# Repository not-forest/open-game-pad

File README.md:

# Open Game Pad

Low-cost, DIY game controller. This project enables anyone to build a custom game pad using affordable components and open hardware principles. The repository contains all necessary files, including PCB designs and firmware.

## Contents
- `pcb/`: PCB design files
- `src/`: Firmware source code
- `usbdrv/`: USB driver files
- `docs/`: Images

## Images

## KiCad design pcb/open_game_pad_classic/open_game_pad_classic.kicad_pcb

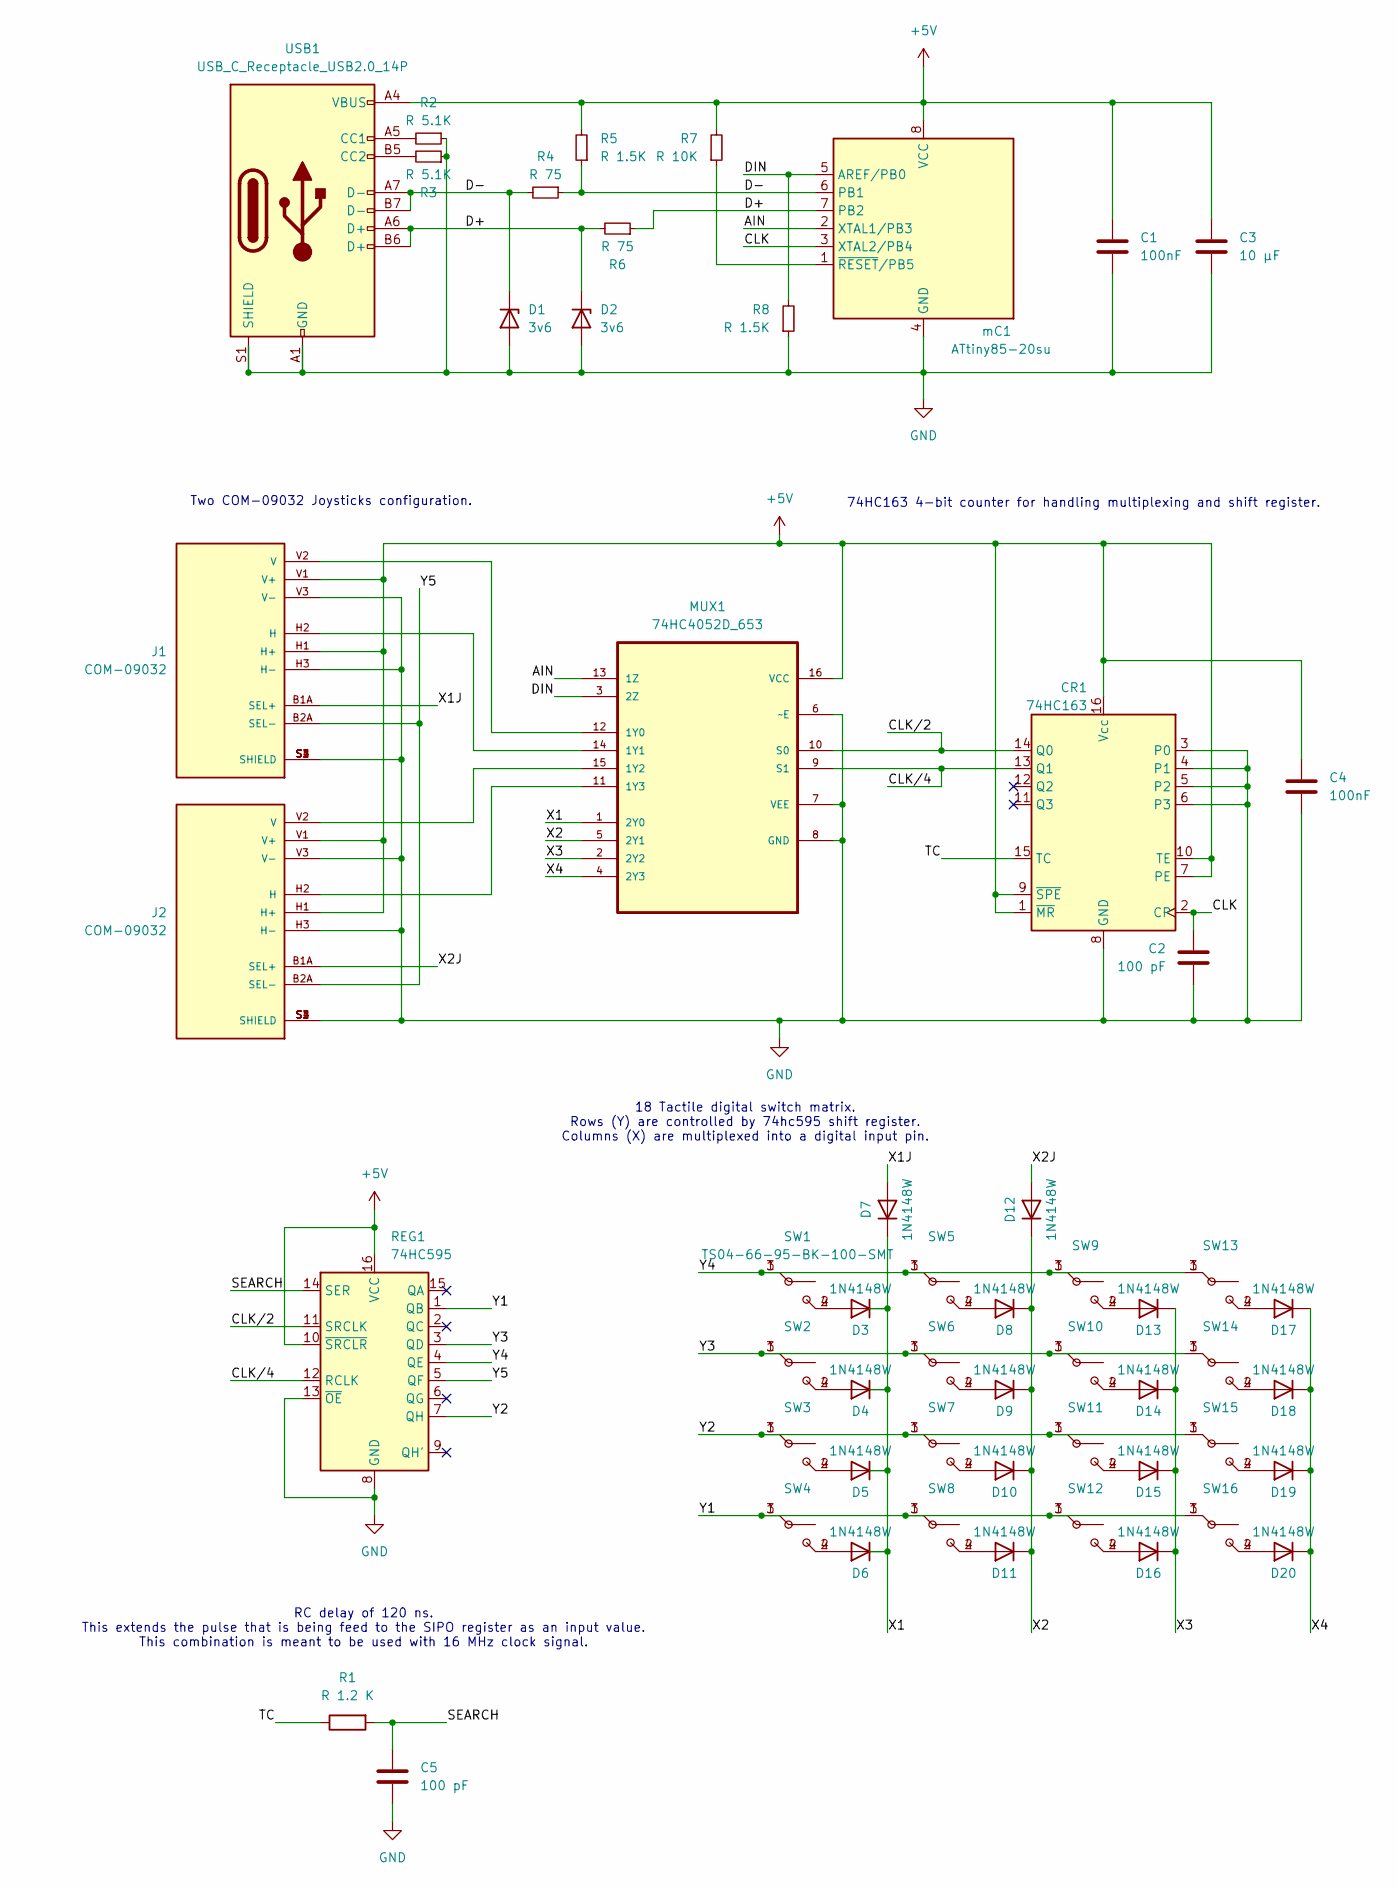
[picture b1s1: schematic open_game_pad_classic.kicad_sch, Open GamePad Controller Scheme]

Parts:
C1, C4: 100nF; C_0402_1005Metric
C2, C5: 100 pF; C_0402_1005Metric
C3: 10 µF; C_0402_1005Metric
CR1: 74HC163; SOIC127P600X175-16N
D1: 3v6; D_0201_0603Metric
D2: 3v6; D_0603_1608Metric
D3, D4, D5, D6, D7, D8, D9, D10, D11, D12, D13, D14, D15, D16, D17, D18, D19, D20: 1N4148W; D_SOD-123
J1, J2: COM-09032; XDCR_COM-09032; PARTREV N/A
MUX1: 74HC4052D_653; SOIC127P600X175-16N; MPN 74HC4052D,653
R1: R 1.2 K; R_0201_0603Metric
R2, R3: R 5.1K; R_0402_1005Metric
R4, R6: R 75; R_0201_0603Metric
R5: R 1.5K; R_0201_0603Metric
R7: R 10K; R_0402_1005Metric
R8: R 1.5K; R_0402_1005Metric
REG1: 74HC595; SOIC127P600X175-16N
SW1: TS04-66-95-BK-100-SMT; SW_TS04-66-95-BK-100-SMT
SW2, SW3, SW4, SW5, SW6, SW7, SW8, SW9, SW10, SW11, SW12, SW13, SW14, SW15, SW16: SW_TS04-66-95-BK-100-SMT
USB1: USB_C_Receptacle_USB2.0_14P; USB_C_Receptacle_HCTL_HC-TYPE-C-16P-01A
mC1: ATtiny85-20su; SOIC127P798X216-8N

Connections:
+5V: C1.1, C3.1, C4.1, CR1.1 (~MR), CR1.7 (PE), CR1.9 (~SPE), CR1.10 (TE), CR1.16 (Vcc), J1.H1 (H+), J1.V1 (V+), J2.H1 (H+), J2.V1 (V+), MUX1.16 (VCC), R5.2, R7.2, REG1.10 (~SRCLR), REG1.16 (VCC), USB1.A4 (VBUS), USB1.A9 (VBUS), USB1.B4 (VBUS), USB1.B9 (VBUS), mC1.8 (VCC)
/AIN: MUX1.13 (1Z), mC1.2 (XTAL1/PB3)
/CLK: C2.1, CR1.2 (CP), mC1.3 (XTAL2/PB4)
/CLK/2: CR1.14 (Q0), MUX1.10 (S0), REG1.11 (SRCLK)
/CLK/4: CR1.13 (Q1), MUX1.9 (S1), REG1.12 (RCLK)
/D+: D2.1 (K), R6.1, R6.2, USB1.A6 (D+), USB1.B6 (D+), mC1.7 (PB2)
/D-: D1.1 (K), R4.1, R4.2, R5.1, USB1.A7 (D-), USB1.B7 (D-), mC1.6 (PB1)
/DIN: MUX1.3 (2Z), R8.2, mC1.5 (AREF/PB0)
/SEARCH: C5.1, R1.2, REG1.14 (SER)
/TC: CR1.15 (TC), R1.1
/X1: D3.1 (K), D4.1 (K), D5.1 (K), D6.1 (K), D7.1 (K), MUX1.1 (2Y0)
/X1J: D7.2 (A), J1.B1A (SEL+)
/X2: D8.1 (K), D9.1 (K), D10.1 (K), D11.1 (K), D12.1 (K), MUX1.5 (2Y1)
/X2J: D12.2 (A), J2.B1A (SEL+)
/X3: D13.1 (K), D14.1 (K), D15.1 (K), D16.1 (K), MUX1.2 (2Y2)
/X4: D17.1 (K), D18.1 (K), D19.1 (K), D20.1 (K), MUX1.4 (2Y3)
/Y1: REG1.1 (QB), SW4.1 (A), SW4.3 (B), SW8.1 (A), SW8.3 (B), SW12.1 (A), SW12.3 (B), SW16.1 (A), SW16.3 (B)
/Y2: REG1.7 (QH), SW3.1 (A), SW3.3 (B), SW7.1 (A), SW7.3 (B), SW11.1 (A), SW11.3 (B), SW15.1 (A), SW15.3 (B)
/Y3: REG1.3 (QD), SW2.1 (A), SW2.3 (B), SW6.1 (A), SW6.3 (B), SW10.1 (A), SW10.3 (B), SW14.1 (A), SW14.3 (B)
/Y4: REG1.4 (QE), SW1.1 (A), SW1.3 (B), SW5.1 (A), SW5.3 (B), SW9.1 (A), SW9.3 (B), SW13.1 (A), SW13.3 (B)
/Y5: J1.B2A (SEL-), J2.B2A (SEL-), REG1.5 (QF)
GND: C1.2, C2.2, C3.2, C4.2, C5.2, CR1.3 (P0), CR1.4 (P1), CR1.5 (P2), CR1.6 (P3), CR1.8 (GND), D1.2 (A), D2.2 (A), J1.H3 (H-), J1.S1 (SHIELD), J1.S2 (SHIELD), J1.S3 (SHIELD), J1.S4 (SHIELD), J1.V3 (V-), J2.H3 (H-), J2.S1 (SHIELD), J2.S2 (SHIELD), J2.S3 (SHIELD), J2.S4 (SHIELD), J2.V3 (V-), MUX1.6 (~E), MUX1.7 (VEE), MUX1.8 (GND), R2.1, R3.1, R8.1, REG1.8 (GND), REG1.13 (~OE), USB1.A1 (GND), USB1.A12 (GND), USB1.B1 (GND), USB1.B12 (GND), USB1.S1 (SHIELD), mC1.4 (GND)
unnamed: D3.2 (A), SW1.2 (A), SW1.4 (B)
unnamed: D4.2 (A), SW2.2 (A), SW2.4 (B)
unnamed: D5.2 (A), SW3.2 (A), SW3.4 (B)
unnamed: D6.2 (A), SW4.2 (A), SW4.4 (B)
unnamed: D8.2 (A), SW5.2 (A), SW5.4 (B)
unnamed: D9.2 (A), SW6.2 (A), SW6.4 (B)
unnamed: D10.2 (A), SW7.2 (A), SW7.4 (B)
unnamed: D11.2 (A), SW8.2 (A), SW8.4 (B)
unnamed: D13.2 (A), SW9.2 (A), SW9.4 (B)
unnamed: D14.2 (A), SW10.2 (A), SW10.4 (B)
unnamed: D15.2 (A), SW11.2 (A), SW11.4 (B)
unnamed: D16.2 (A), SW12.2 (A), SW12.4 (B)
unnamed: D17.2 (A), SW13.2 (A), SW13.4 (B)
unnamed: D18.2 (A), SW14.2 (A), SW14.4 (B)
unnamed: D19.2 (A), SW15.2 (A), SW15.4 (B)
unnamed: D20.2 (A), SW16.2 (A), SW16.4 (B)
unnamed: J1.H2 (H), MUX1.14 (1Y1)
unnamed: J1.V2 (V), MUX1.12 (1Y0)
unnamed: J2.H2 (H), MUX1.11 (1Y3)
unnamed: J2.V2 (V), MUX1.15 (1Y2)
unnamed: R2.2, USB1.A5 (CC1)
unnamed: R3.2, USB1.B5 (CC2)
unnamed: R7.1, mC1.1 (~RESET/PB5)

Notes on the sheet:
18 Tactile digital switch matrix. Rows (Y) are controlled by 74hc595 shift register. Columns (X) are multiplexed into a digital input pin.
74HC163 4-bit counter for handling multiplexing and shift register.
RC delay of 120 ns. This extends the pulse that is being feed to the SIPO register as an input value. This combination is meant to be used with 16 MHz clock signal.
Two COM-09032 Joysticks configuration.

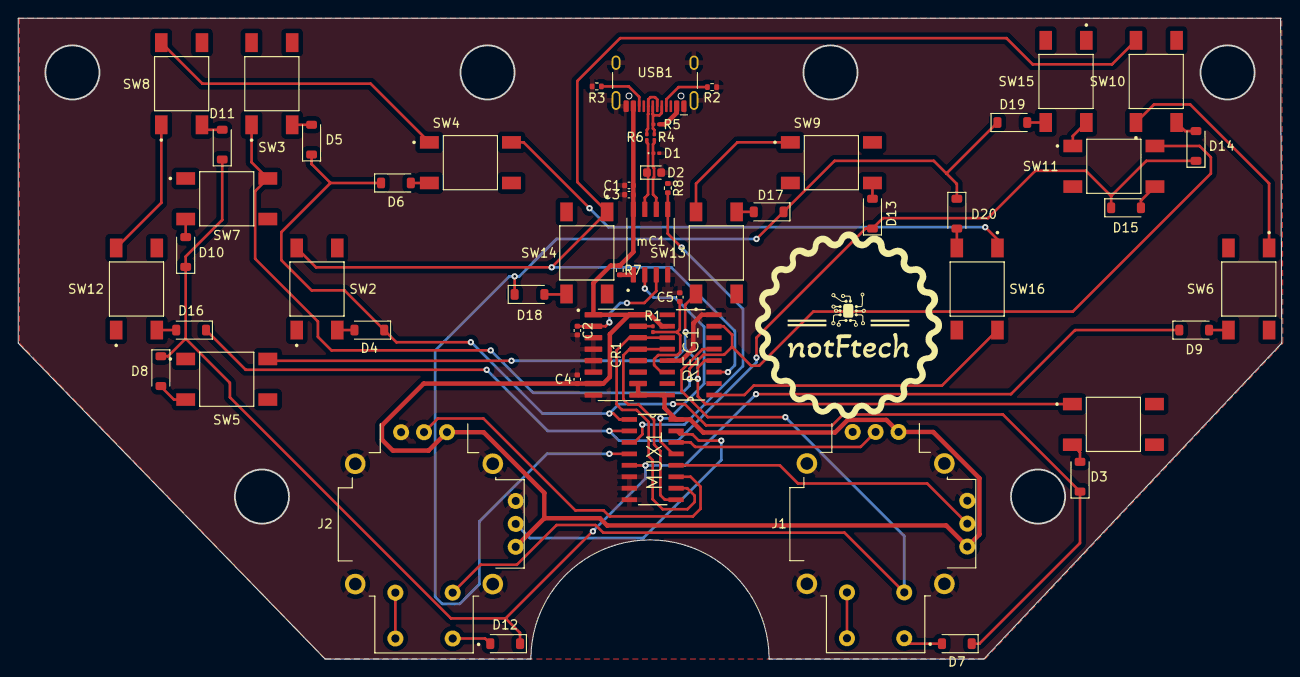
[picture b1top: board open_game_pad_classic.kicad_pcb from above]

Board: 2 copper layers, 139.9 x 70.9 mm, 56 parts (0 on the bottom side), 45 nets.

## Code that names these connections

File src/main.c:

/* 
 *  Main firmware code for 'Open Game Pad'
 *
 *  This code defines all necessary functions and stuctures for operating data between input sensors and output USB connector.
 *  The code is interrupt driven, therefore all necessary initialization part can be found in main function, while the rest is
 *  located in ISR definitions. V-USB library is a main driver for communicating with a host device as a hid device.
 *
 * */
 
#include<avr/pgmspace.h>
#include<avr/interrupt.h>

#include<avr/delay.h>
#include<avr/wdt.h>
#include<avr/io.h>

#include "../usbdrv/usbdrv.h"
#include "ogpad.h"

// Pointer to the REPORT structure.
static report_t *RPTR = &REPORT;
// Determines how often the device should send a report to the host when there is no change in the state of the inputs.
static uchar IDLE_RATE;
// Inpur counter allows to define which key we are reading as a digital input or which axis as an analog input.
static volatile inputCounter ic = { .raw = 0 };

/* 
 * Game Pad report descriptor. 
 *
 * It defines a device's buttons and joysticks via USB report descriptor. 
 * */
PROGMEM const char usbDescriptorHidReport[USB_CFG_HID_REPORT_DESCRIPTOR_LENGTH] = {
    // Global information.
    0x05, 0x01,                    // USAGE_PAGE (Generic Desktop)
    0x09, 0x05,                    // USAGE (Gamepad)
    0xA1, 0x01,                    // COLLECTION (Application)
    0xA1, 0x00,                    //   COLLECTION (Physical)
    // 18 buttons handling.
    0x05, 0x09,                    //     USAGE_PAGE (Button)
    0x19, 0x01,                    //     USAGE_MINIMUM (Button 1)
    0x29, 0x12,                    //     USAGE_MAXIMUM (Button 18)
    0x15, 0x00,                    //     LOGICAL_MINIMUM (0)
    0x25, 0x01,                    //     LOGICAL_MAXIMUM (1)
    0x95, 0x12,                    //     REPORT_COUNT (18)
    0x75, 0x01,                    //     REPORT_SIZE (1)
    0x81, 0x02,                    //     INPUT (Data,Var,Abs)
    // Unused bits are ignored.
    0x95, 0x01,                    //     REPORT_COUNT (1)
    0x75, 0x0D,                    //     REPORT_SIZE (14)
    0x81, 0x03,                    //     INPUT (Cnst,Var,Abs)
    // Joysticks handling.
    0x05, 0x01,                    //     USAGE_PAGE (Generic Desktop)
    0x09, 0x30,                    //     USAGE (X)
    0x09, 0x31,                    //     USAGE (Y)
    0x09, 0x32,                    //     USAGE (Z)
    0x09, 0x33,                    //     USAGE (Rx)
    0x15, 0x81,                    //     LOGICAL_MINIMUM (-127)
    0x25, 0x7F,                    //     LOGICAL_MAXIMUM (127)
    0x75, 0x08,                    //     REPORT_SIZE (8)
    0x95, 0x04,                    //     REPORT_COUNT (4)
    0x81, 0x02,                    //     INPUT (Data,Var,Abs)
    // Closing collections.
    0xC0,                          //   END_COLLECTION
    0xC0                           // END_COLLECTION
};

// This is the function from the V-USB library that must be defined here to properly handle the requests from the host.
usbMsgLen_t usbFunctionSetup(uchar raw[8]) {
    usbRequest_t *req = (void *) raw;

    // Class request type.
    if((req->bmRequestType & USBRQ_TYPE_MASK) == USBRQ_TYPE_CLASS){
        if(req->bRequest == USBRQ_HID_GET_REPORT){  /* wValue: ReportType (highbyte), ReportID (lowbyte) */
            // we only have one report type, so don't look at wValue
            usbMsgPtr = (void *) RPTR;
            return sizeof(REPORT);
        }else if(req->bRequest == USBRQ_HID_GET_IDLE){
            usbMsgPtr = &IDLE_RATE;
            return 1;
        }else if(req->bRequest == USBRQ_HID_SET_IDLE){
            IDLE_RATE = req->wValue.bytes[1];
        }
    }else{
        /* Vendor specific requests could be implemented here to built up the firmware abilities. */
    } 

    return 0;
}

#define abs(x) ((x) > 0 ? (x) : (-x))

// Calibrates the RC oscillator to 16.5 MHz speeds.
void hadUsbReset(void) {
    int frameLength, targetLength = (unsigned)(1499 * (double)F_CPU / 10.5e6 + 0.5);
    int bestDeviation = 9999;
    uchar trialCal, bestCal, step, region;

    // do a binary search in regions 0-127 and 128-255 to get optimum OSCCAL
    for(region = 0; region <= 1; region++) {
        frameLength = 0;
        trialCal = (region == 0) ? 0 : 128;
        
        for(step = 64; step > 0; step >>= 1) { 
            if(frameLength < targetLength) // true for initial iteration
                trialCal += step; // frequency too low
            else
                trialCal -= step; // frequency too high
                
            OSCCAL = trialCal;

            cli();
            frameLength = usbMeasureFrameLength();
            sei();

            if(abs(frameLength-targetLength) < bestDeviation) {
                bestCal = trialCal; // new optimum found
                bestDeviation = abs(frameLength -targetLength);
            }
        }
    }

    OSCCAL = bestCal;
}

// Main function that initializes registers with required values and then waits for interrupts.
int __attribute__((noreturn)) main(void) {
    wdt_disable();
    /*      GPIO Configuration      */
    // PB1, PB2 lines are handled by V-USB. PB0 is a digital input line by default. 
    // The clock is being bit-banged inside the ADC interrupt handler.
    DDRB = 1 << PB4;        // CLK output.
    PCMSK = 1 << PCINT0;    // The PCINT interrupt will be invoked only when something changes on PB0.

    /*      ADC Configuration       */
    // - Only 8 highest bits are required, therefore 1 Mhz sampling can be used for faster conversion. This sampling is a limit declared 
    // in the datasheet;
    // - Holding high bits in ADCH as a result;
    // - Single ended input with internal Vcc voltage reference is being used;
    ADCSRA = (1 << ADPS2) | (1 << ADSC) | (1 << ADIF);
    ADMUX = (1 << MUX1) | (1 << MUX0) | (1 << ADLAR);

    wdt_enable(WDTO_1S);                   // Enabling the watchdog timer and selecting the 1s expiring.
    
    usbDeviceDisconnect();                    // Forcing re-enumeration.
    wdt_reset();                           // One second is enough for the next step.
    uchar i = 0;
    while(--i){             // USB would be disconnected for 300 ms.
        wdt_reset();
        _delay_ms(1);
    }                       
    usbDeviceConnect();
    usbInit();                             // Start of USB handling.

    GIMSK = 1 << PCIE;
    // Main loop only handles the USB connection and resets the watchdog timer.
    sei();
    for(;;) {
        wdt_reset();
        usbPoll();                         // Polling the USB lines
        
        // Here we are sending the current data we have.
        if(usbInterruptIsReady()) {        // If interrupt is ready, sending the newest data.
            usbSetInterrupt((void *) RPTR, sizeof(REPORT));
        }
    }
}

/* 
 * This interrupt handles ADC data on AIN line. 
 *
 * It also does the output clock control by bitbanging, so all outside components are dependent on
 * ADC convertion. This way it is possible to decode all digital and analog inputs.
 * */
ISR(ADC_vect) {
    PORTB ^= (1 << PB4);                          // Clock tick.
    RPTR->joyax[ic.ANALOG] = ADCH;                // Writing the next analog input to the proper location.
    ADCSRA |= (1 << ADSC);                        // Starting new ADC conversion.
    ic.raw++;

    if(ic.raw > 18) ic.raw = 0;
}

/* 
 * Sets an interrupt for the PB0 pin. 
 * 
 * INT0 is reserved for the V-USB use. The PCINT[5..0] would cause this interrupt.
 * This handler detects a keypress obtained from the key matrix and iterates over each key to
 * define which key was pressed. All pressed keys are then saved into a mask and send via USB
 * connection.
 * */
ISR(PCINT0_vect) {
    RPTR->bmask = (PORTB & 1) << ic.DIGITAL;      // Marking the value in the button mask. This way several keys can be pressed in one loop.
}

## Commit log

2024-06-02 Added template files for initial setup.
2024-06-02 Compile commands with bear utility.
2024-06-02 Added compile script for creating raw hex code.
2024-06-06 First PCB scheme version designed. Many changes possible
2024-06-07 Connected required libraries. Added the device report descriptor.
2024-06-07 Added more footprints for switches.
2024-06-07 Filled the usbconfig according to V-USB.
2024-06-07 Added V-USB library to project's scope.
2024-06-10 Added an inverting amplifier circuit to convert a -2.5V +2.5V signal to 0V - 5V for further use in ADC converter.
2024-06-11 Minor changes to register values and their footprint
2024-06-19 Updated the PCB and scheme. 2-layered, ground plane.
2024-06-19 Provided a refined version of USB HID report type.
2024-06-19 Added Makefile from V-USB library examples with minor tweaks.
2024-06-19 Changed the configuration based on the new USB HID report descriptor.
2024-06-19 Implemented the starter main function logic. Changed the USB HID report descriptor to a version that is expected by a host device. Initializing the V-USB library.
2024-06-19 The bash script is now replaced with a Makefile.
2024-06-20 More decoupling for microcontroller and timer.
2024-06-20 Fixed the schematic on PISO read. Updated the PCB.
2024-06-20 Fixed the reset problem by adding an 8-tick delay.
2024-06-20 Changed the report to be packed. Now joysticks are defined in array for less code.
2024-06-20 Minor fixes for the clean
2024-06-20 Added the main functionality. Reading the multiplexed analog data from the joystick axis.
2024-06-27 Removed the obsolete parts. Changed the logic completely to use one SIPO register. Using external counter to plex four analog and four digital inputs in one double 74hc4052.
2024-06-27 Imported footprints.
2024-06-28 Optimized the report structure so that overall size is a power of two.
2024-06-28 Changed the code based on new schematic. Updated the USB report based on new structure.
2024-06-28 Removed unnecessary files.
2024-06-29 Updated the PCB based on the new schematic design.
2024-06-30 Deleted uneccessary files.
2024-06-30 Added drill holes. Changes in design for better timing in a differential pair for USB transmision.
2024-06-30 Added the logo.
2024-07-01 Fixed the 3d models kicad bug.
2024-07-01 Removed the legacy version.
2024-07-09 Fixed the switches connections and remade the tracks in pcb.
2024-07-09 todo
2024-07-10 Fixed the schematic logic. Added a RC delay circuit to feed a short TC signal to the SIPO register. This allows for matrix scan based fully on clock. This component is intended to be used with ATtiny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
2024-08-10 Fixed the '16Mhz' fuse.
2024-08-10 Removing the descriptor size constant.
2024-08-10 Changed the USB poll interval and maximal power consumed by usb bus. Added a reset hook reference for reset RC calibration function.
2024-08-10 Added a function that calibrates 16.5MHz by optimizing OSCCAL value in two regions.
2024-08-13 Updates the PCB according to new schematic.
2024-10-20 Added readme and images.
